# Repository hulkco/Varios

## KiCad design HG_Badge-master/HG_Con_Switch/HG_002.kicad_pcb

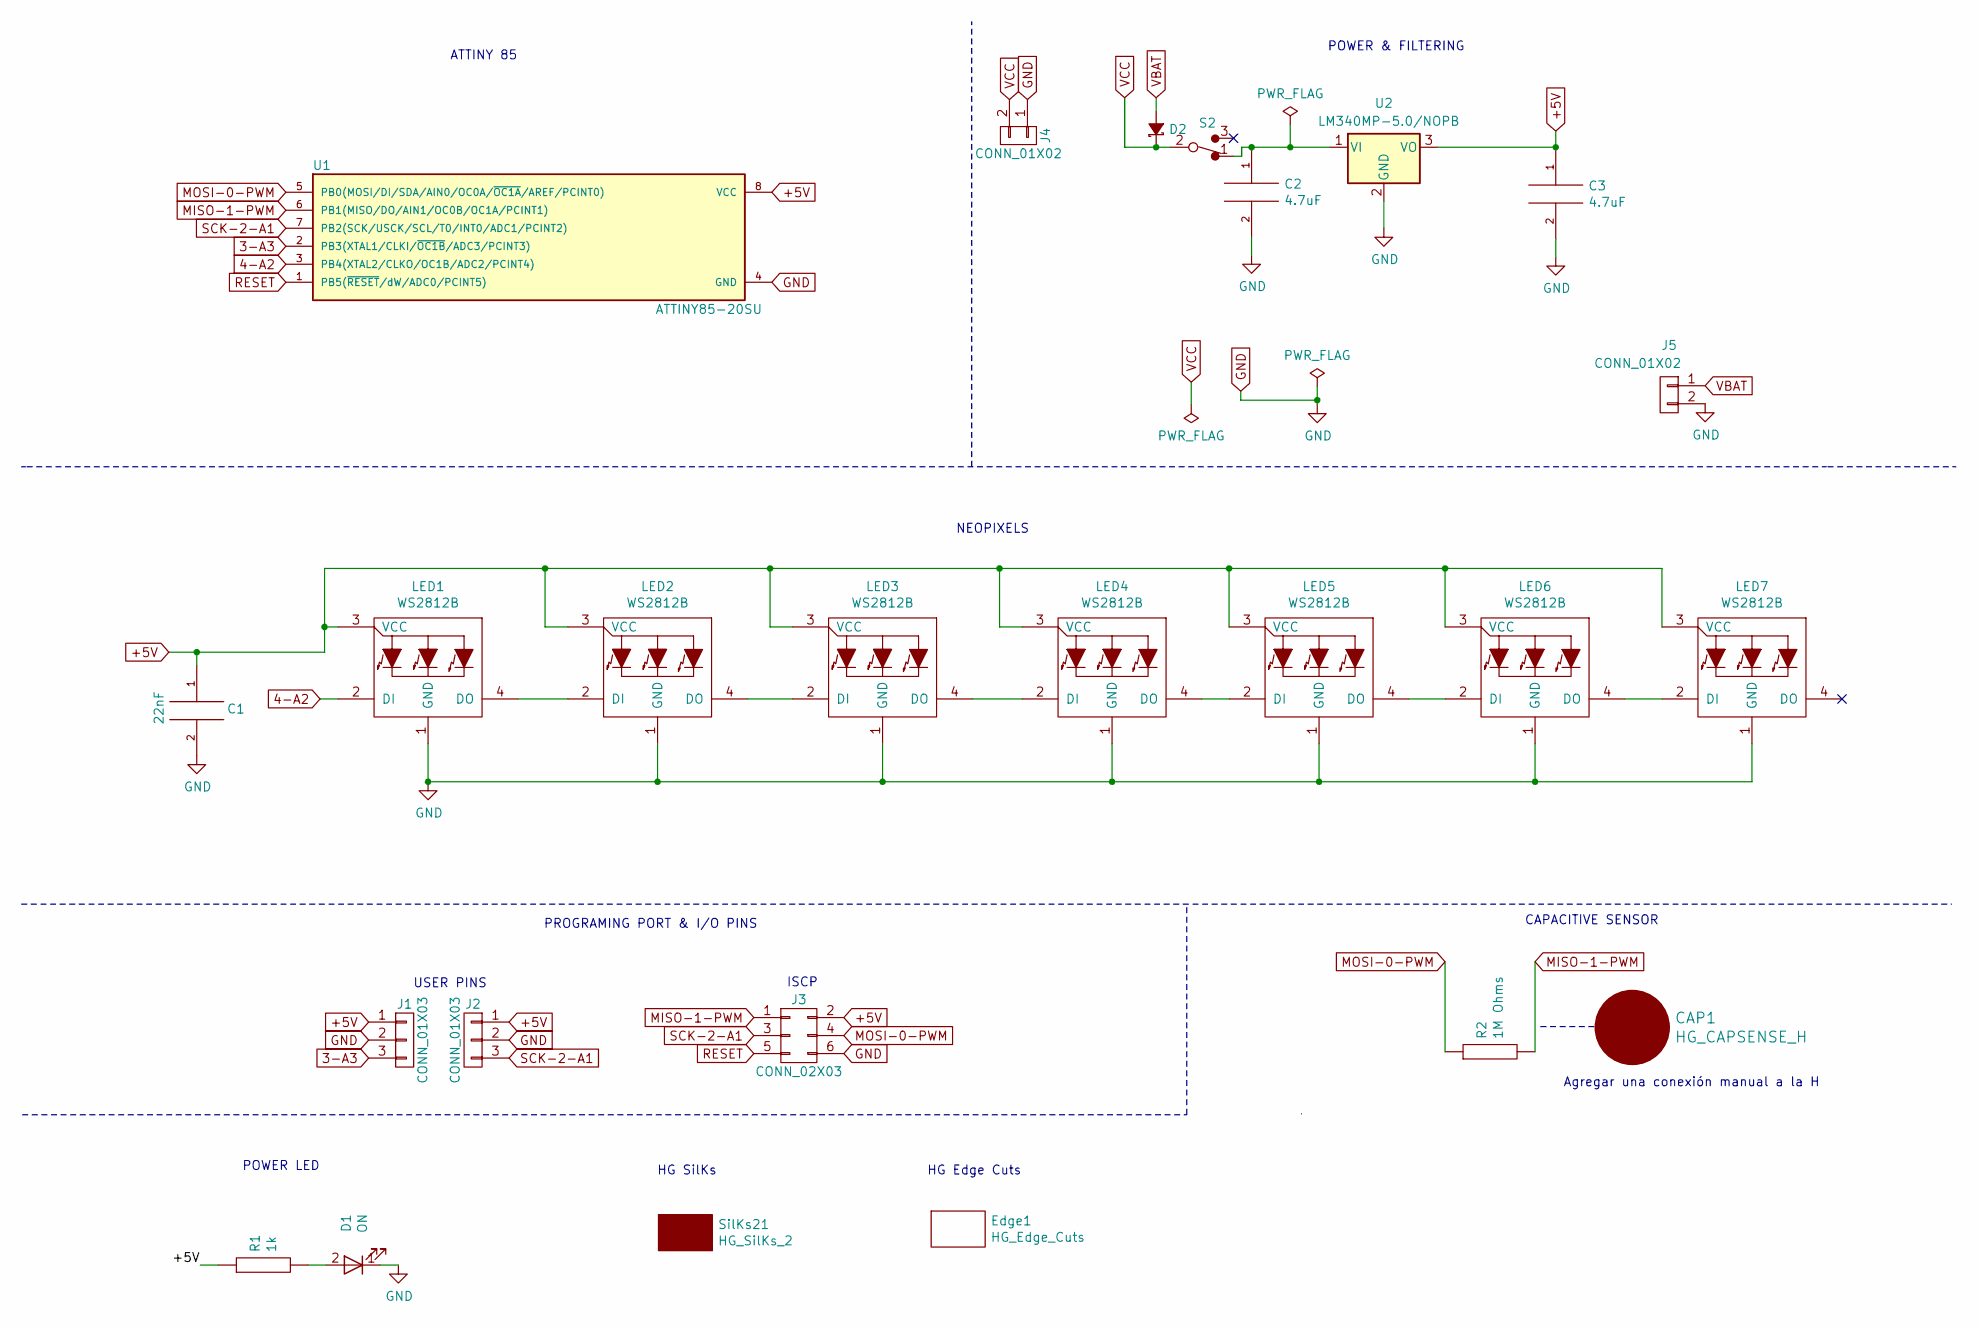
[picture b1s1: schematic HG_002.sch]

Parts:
C1: 22nF; C_1206_HandSoldering
C2, C3: 4.7uF; C_1206_HandSoldering
CAP1: HG_CAPSENSE_H; H_CapSense
D1: ON; LED_1206_HandSoldering
D2: MBRA140; DIODE-SMA
Edge1: HG_Edge_Cuts; HG_100_Edge_Cuts
J1: CONN_01X03; Pin_Header_Straight_1x03_Pitch2.54mm_SMD_Pin1Left
J2: CONN_01X03; Pin_Header_Straight_1x03_Pitch2.54mm_SMD_Pin1Right
J3: CONN_02X03; Pin_Header_Straight_2x03_Pitch2.54mm_SMD
J4: CONN_01X02; Pin_Header_Straight_1x02_Pitch2.54mm_SMD_Pin1Left
J5: CONN_01X02; Molex_PicoBlade_53261-0271_02x1.25mm_Angled
LED1, LED2, LED3, LED4, LED5, LED6, LED7: WS2812B
R1: 1k; R_1206_HandSoldering
R2: 1M Ohms; R_1206_HandSoldering
S2: MSK12C02_SWITCH-SLIDE-SPDT; MSK12C02
SilKs21: HG_SilKs_2; Corona_SilKs_3
U1: ATTINY85-20SU; SOIJ-8_5.3x5.3mm_Pitch1.27mm
U2: LM340MP-5.0/NOPB; SOT-223-3Lead_TabPin2

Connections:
3-A3: J1.3, U1.2 (PB3(XTAL1/CLKI/~OC1B~/ADC3/PCINT3))
4-A2: LED1.2 (DI), U1.3 (PB4(XTAL2/CLKO/OC1B/ADC2/PCINT4))
+5V: C1.1, C3.1, J1.1, J2.1, J3.2, LED1.3 (VCC), LED2.3 (VCC), LED3.3 (VCC), LED4.3 (VCC), LED5.3 (VCC), LED6.3 (VCC), LED7.3 (VCC), R1.1, U1.8 (VCC), U2.3 (VO)
GND: C1.2, C2.2, C3.2, D1.1 (K), J1.2, J2.2, J3.6, J4.1, J5.2, LED1.1 (GND), LED2.1 (GND), LED3.1 (GND), LED4.1 (GND), LED5.1 (GND), LED6.1 (GND), LED7.1 (GND), U1.4 (GND), U2.2 (GND)
MISO-1-PWM: J3.1, R2.2, U1.6 (PB1(MISO/DO/AIN1/OC0B/OC1A/PCINT1))
MOSI-0-PWM: J3.4, R2.1, U1.5 (PB0(MOSI/DI/SDA/AIN0/OC0A/~OC1A~/AREF/P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)
unnamed: C2.1, S2.1, U2.1 (VI)
unnamed: D1.2 (A), R1.2
unnamed: LED1.4 (DO), LED2.2 (DI)
unnamed: LED2.4 (DO), LED3.2 (DI)
unnamed: LED3.4 (DO), LED4.2 (DI)
unnamed: LED4.4 (DO), LED5.2 (DI)
unnamed: LED5.4 (DO), LED6.2 (DI)
unnamed: LED6.4 (DO), LED7.2 (DI)
RESET: J3.5, U1.1 (PB5(~RESET~/dW/ADC0/PCINT5))
SCK-2-A1: J2.3, J3.3, U1.7 (PB2(SCK/USCK/SCL/T0/INT0/ADC1/PCINT2))
VBAT: D2.2 (A), J5.1
VCC: D2.1 (K), J4.2, S2.2

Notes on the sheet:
POWER & FILTERING
ATTINY 85
NEOPIXELS
PROGRAMING PORT & I/O PINS
CAPACITIVE SENSOR
ISCP
USER PINS
POWER LED
HG Edge Cuts
HG SilKs
Agregar una conexión manual a la H

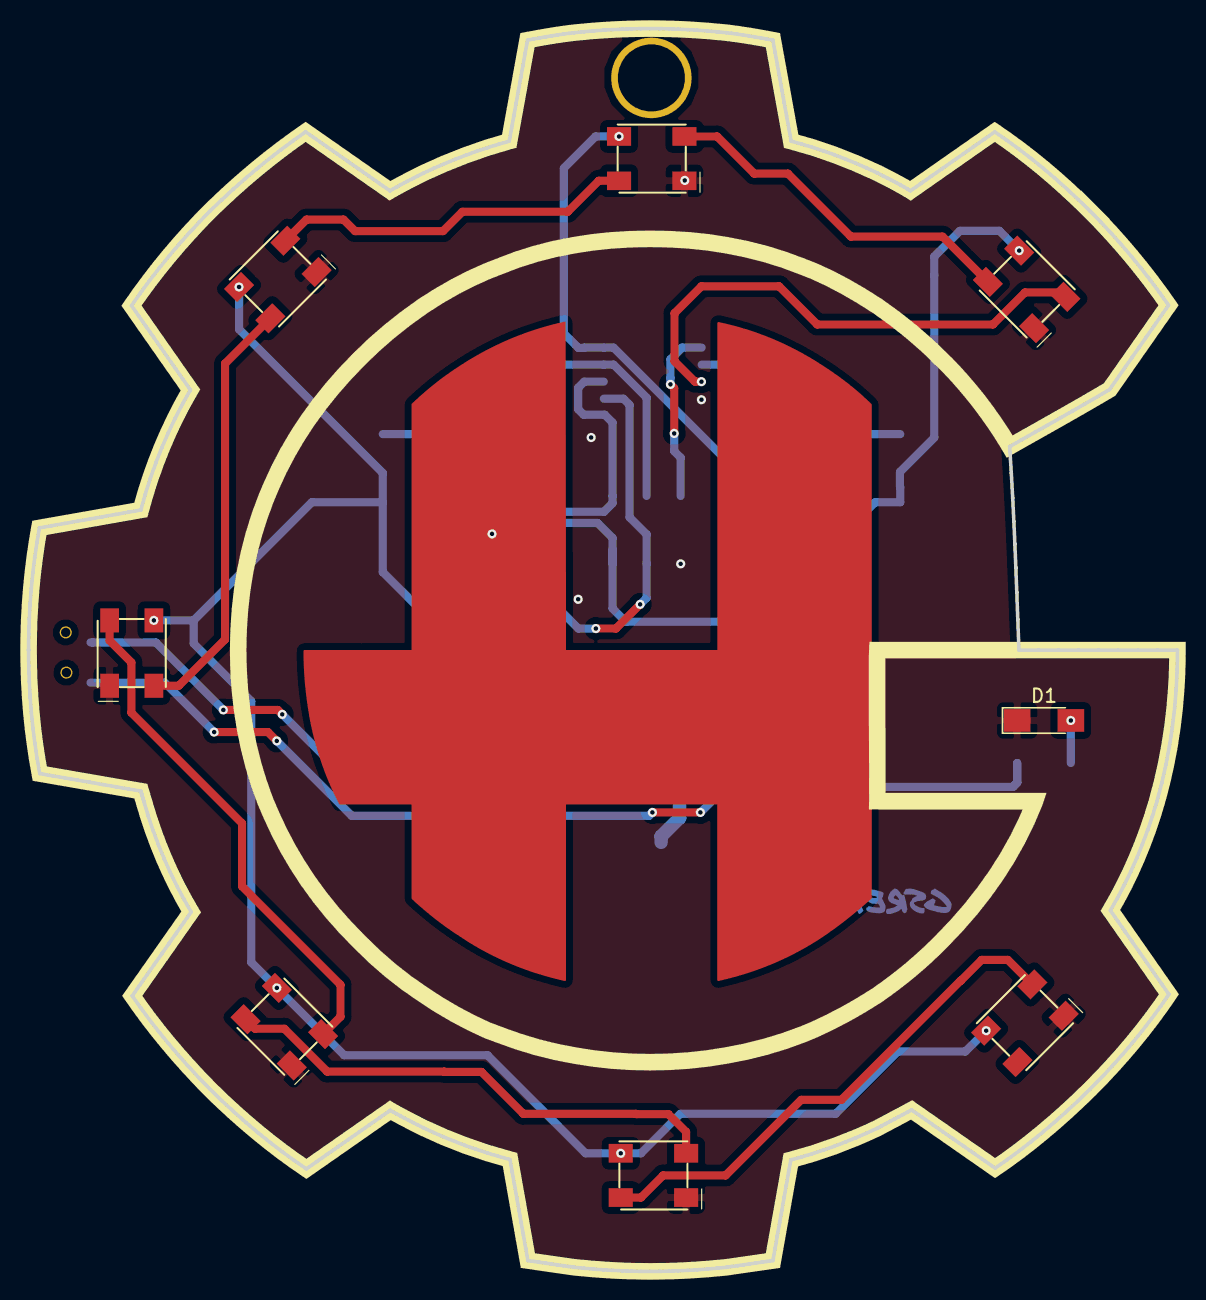
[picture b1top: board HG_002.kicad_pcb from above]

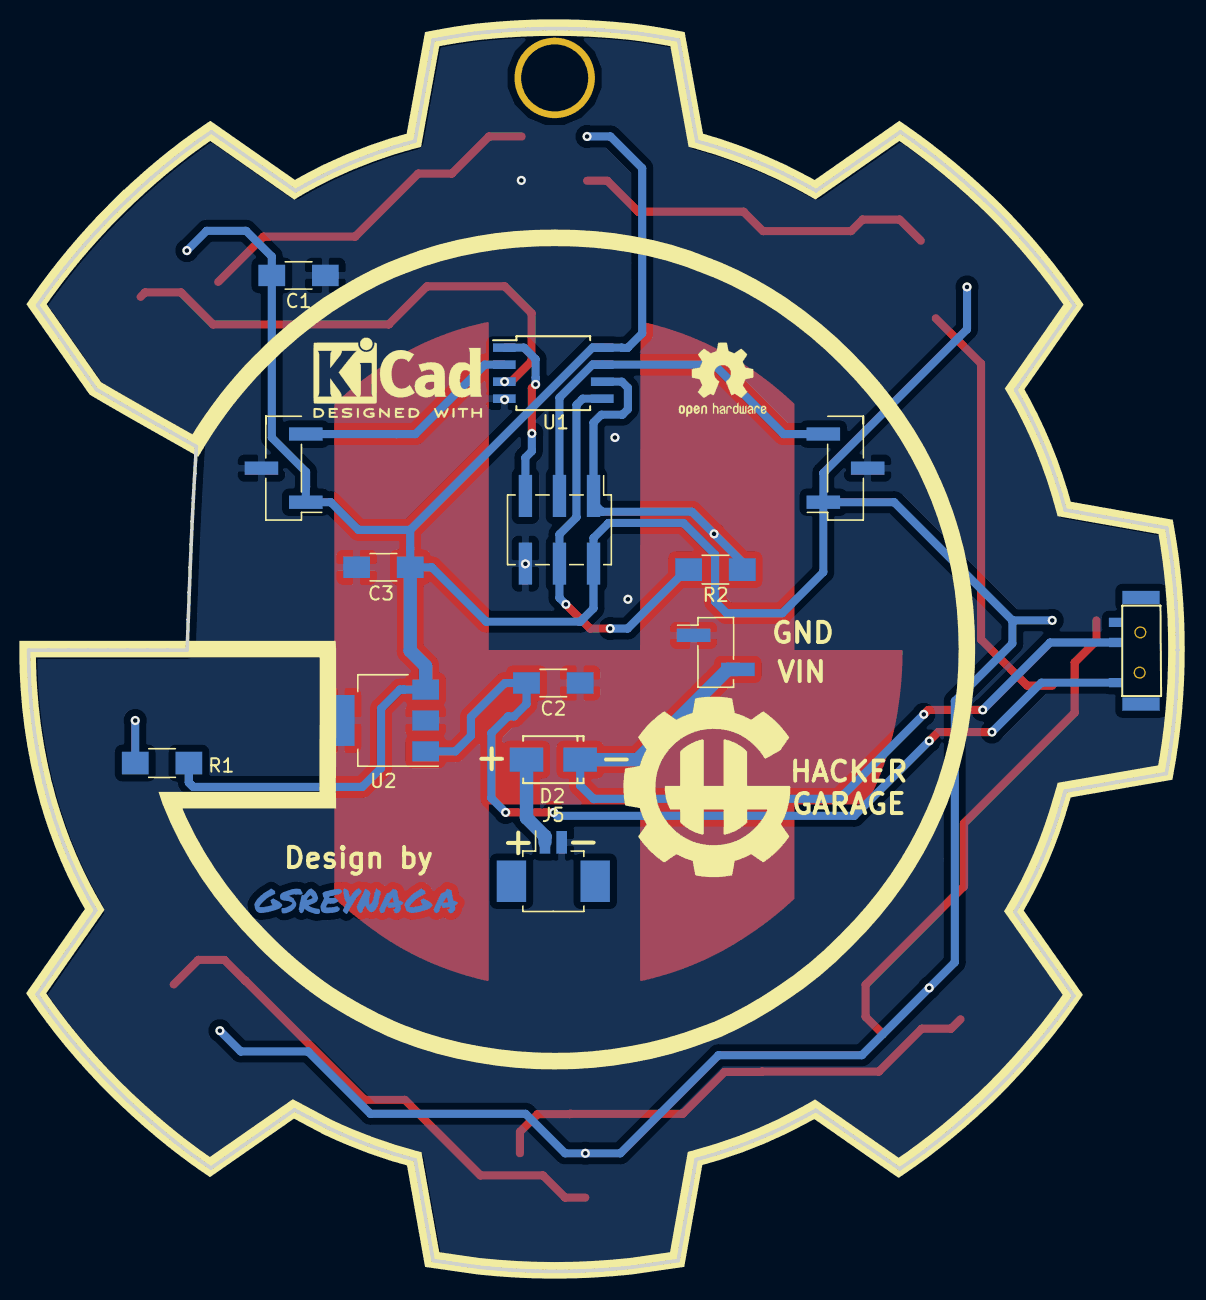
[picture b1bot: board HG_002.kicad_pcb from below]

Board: 2 copper layers, 85.7 x 92.7 mm, 28 parts (17 on the bottom side), 18 nets.

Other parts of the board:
MountinHoleBagde: MountingHole_5mm_Badge; MountingHole_3.5mm_Pad
svg2mod: G***; FirmaCuMask
svg2mod#2: G***; HG_SmallLogo
svg2mod#3: G***; HG_Edge.SilkS.2
svg2mod#4: G***; HG_SilkS.Back.2

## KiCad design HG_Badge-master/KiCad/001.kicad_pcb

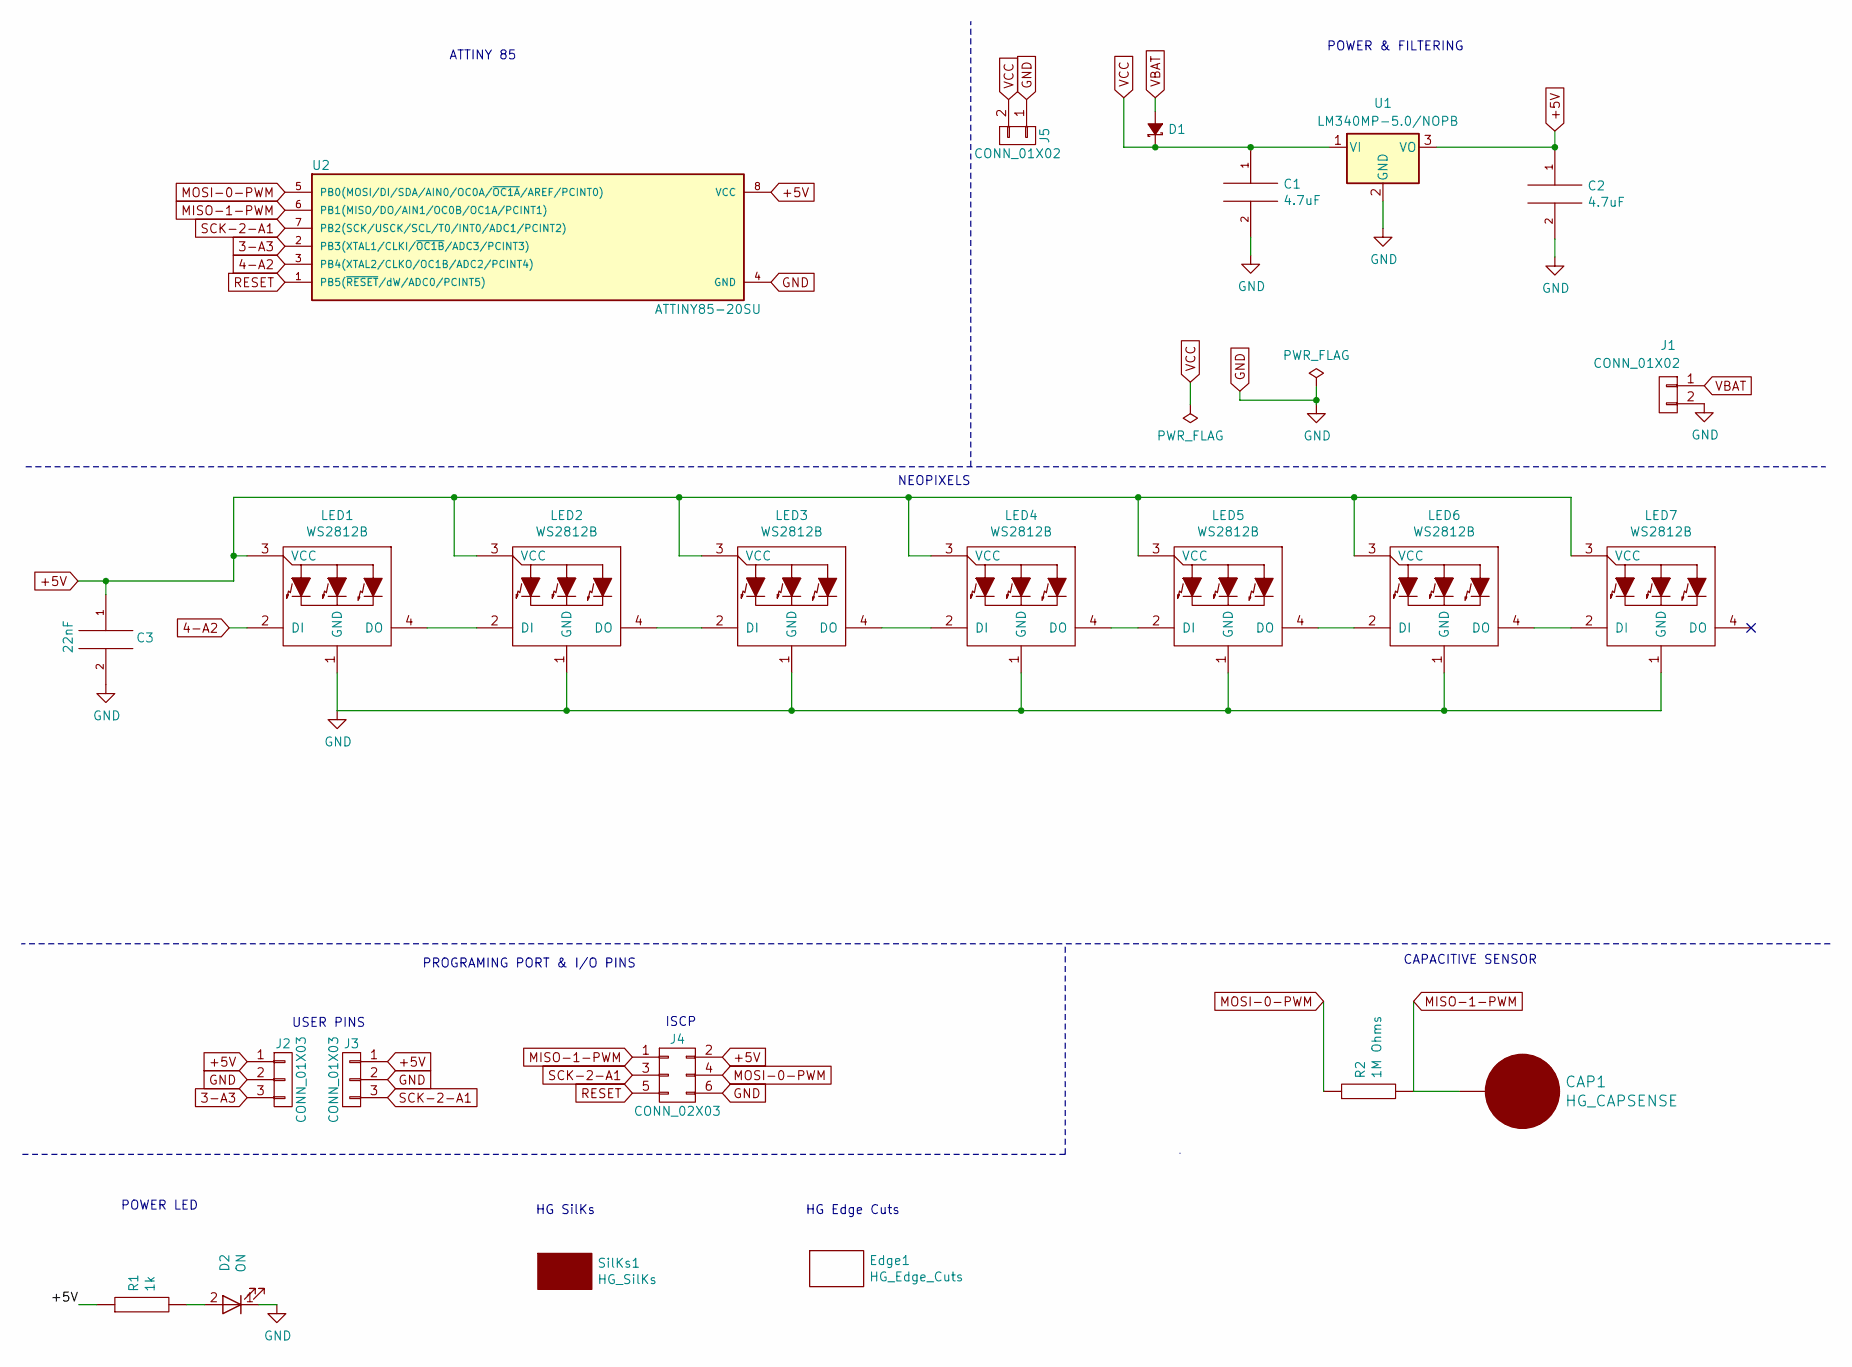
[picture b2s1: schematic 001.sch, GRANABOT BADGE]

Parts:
C1, C2: 4.7uF; C_1206_HandSoldering
C3: 22nF; C_1206_HandSoldering
CAP1: HG_CAPSENSE; H_CapSense
D1: MBRA140; DIODE-SMA
D2: ON; LED_1206_HandSoldering
Edge1: HG_Edge_Cuts; HG_100_Edge_Cuts
J1: CONN_01X02; Molex_PicoBlade_53261-0271_02x1.25mm_Angled
J2: CONN_01X03; Pin_Header_Straight_1x03_Pitch2.54mm_SMD_Pin1Left
J3: CONN_01X03; Pin_Header_Straight_1x03_Pitch2.54mm_SMD_Pin1Right
J4: CONN_02X03; Pin_Header_Straight_2x03_Pitch2.54mm_SMD
J5: CONN_01X02; Pin_Header_Straight_1x02_Pitch2.54mm_SMD_Pin1Left
LED1, LED2, LED3, LED4, LED5, LED6, LED7: WS2812B
R1: 1k; R_1206_HandSoldering
R2: 1M Ohms; R_1206_HandSoldering
SilKs1: HG_SilKs; Corona_SilKs
U1: LM340MP-5.0/NOPB; SOT-223-3Lead_TabPin2
U2: ATTINY85-20SU; SOIJ-8_5.3x5.3mm_Pitch1.27mm

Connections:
3-A3: J2.3, U2.2 (PB3(XTAL1/CLKI/~OC1B~/ADC3/PCINT3))
4-A2: LED1.2 (DI), U2.3 (PB4(XTAL2/CLKO/OC1B/ADC2/PCINT4))
+5V: C2.1, C3.1, J2.1, J3.1, J4.2, LED1.3 (VCC), LED2.3 (VCC), LED3.3 (VCC), LED4.3 (VCC), LED5.3 (VCC), LED6.3 (VCC), LED7.3 (VCC), R1.1, U1.3 (VO), U2.8 (VCC)
GND: C1.2, C2.2, C3.2, D2.1 (K), J1.2, J2.2, J3.2, J4.6, J5.1, LED1.1 (GND), LED2.1 (GND), LED3.1 (GND), LED4.1 (GND), LED5.1 (GND), LED6.1 (GND), LED7.1 (GND), U1.2 (GND), U2.4 (GND)
MISO-1-PWM: CAP1.1, J4.1, R2.2, U2.6 (PB1(MISO/DO/AIN1/OC0B/OC1A/PCINT1))
MOSI-0-PWM: J4.4, R2.1, U2.5 (PB0(MOSI/DI/SDA/AIN0/OC0A/~OC1A~/AREF/P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)
unnamed: D2.2 (A), R1.2
unnamed: LED1.4 (DO), LED2.2 (DI)
unnamed: LED2.4 (DO), LED3.2 (DI)
unnamed: LED3.4 (DO), LED4.2 (DI)
unnamed: LED4.4 (DO), LED5.2 (DI)
unnamed: LED5.4 (DO), LED6.2 (DI)
unnamed: LED6.4 (DO), LED7.2 (DI)
RESET: J4.5, U2.1 (PB5(~RESET~/dW/ADC0/PCINT5))
SCK-2-A1: J3.3, J4.3, U2.7 (PB2(SCK/USCK/SCL/T0/INT0/ADC1/PCINT2))
VBAT: D1.2 (A), J1.1
VCC: C1.1, D1.1 (K), J5.2, U1.1 (VI)

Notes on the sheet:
POWER & FILTERING
ATTINY 85
NEOPIXELS
PROGRAMING PORT & I/O PINS
CAPACITIVE SENSOR
ISCP
USER PINS
POWER LED
HG Edge Cuts
HG SilKs

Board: 2 copper layers, 24 parts (13 on the bottom side), 17 nets, no tracks yet.

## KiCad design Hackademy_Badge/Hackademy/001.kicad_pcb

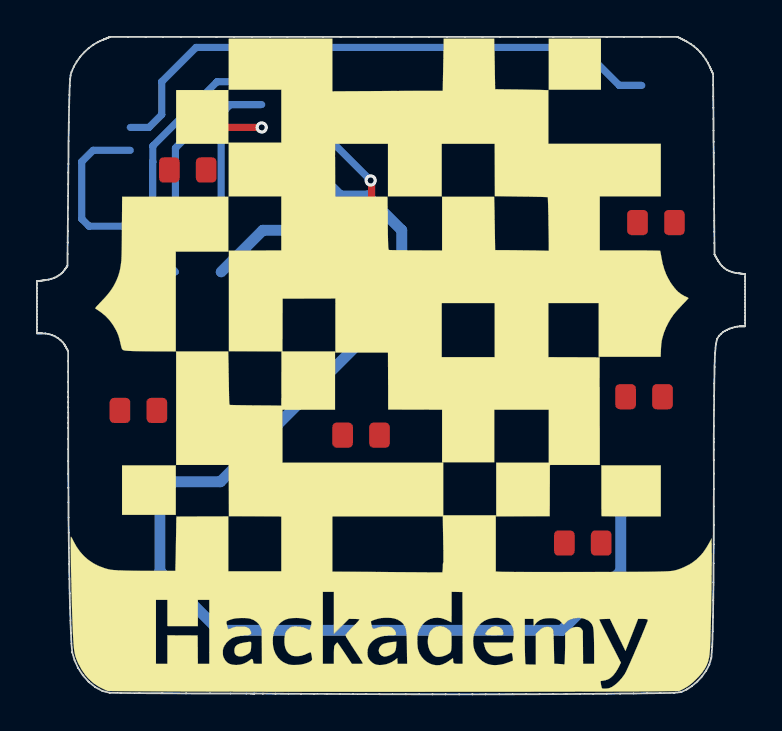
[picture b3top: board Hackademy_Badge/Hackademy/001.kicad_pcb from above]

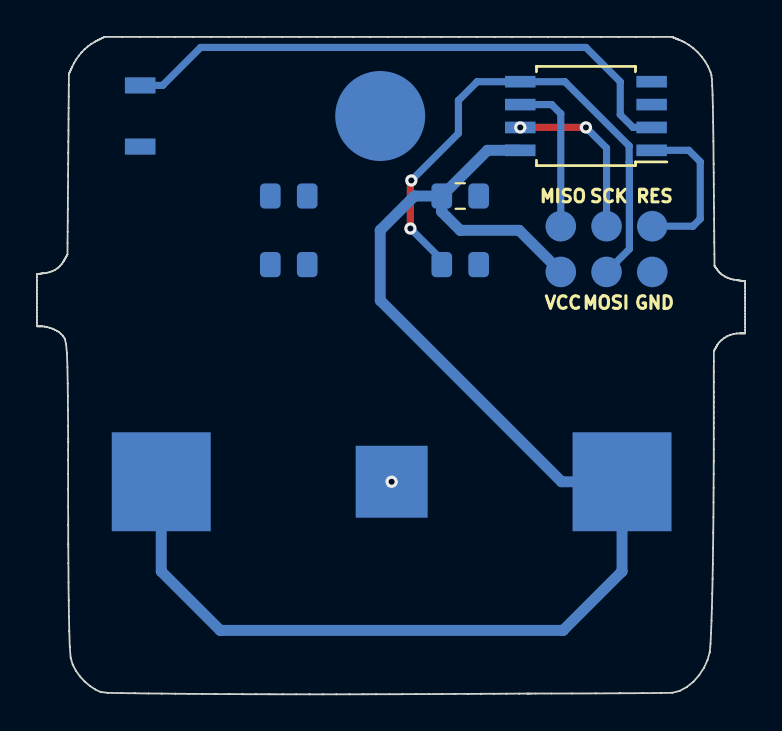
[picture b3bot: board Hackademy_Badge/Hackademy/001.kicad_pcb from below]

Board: 2 copper layers, 39.3 x 36.5 mm, 16 parts (9 on the bottom side), 10 nets.

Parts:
BT1: Battery; S8211R
C1: C_Small; C_0805
D1, D2, D3, D4, D5, D6: LED_Small_ALT; LED_0805
J1: Conn_02x03_Odd_Even; PogoPinSocket_2x03_P2.54mm
R1, R2, R3: 22 ohms; R_0805
Ref1: Edge.Cuts; Hackademy_01
Ref2: PinPad; Pin_Pad_D5.0mm
SW1: SW_Push; SW_SPST_B3U-1000P
U1: ATtiny85-20SU; SOIJ-8_5.3x5.3mm_P1.27mm

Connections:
+3V3: BT1.1, C1.2, J1.2, U1.8
GND: BT1.2, C1.1, J1.6, SW1.2, U1.4
unnamed: D1.1, D2.2, D3.2, D4.1, R2.1
unnamed: D1.2, D2.1, D5.2, D6.1, R1.1
unnamed: D3.1, D4.2, D5.1, D6.2, R3.1
PB0: J1.4, R1.2, U1.5
PB1: J1.1, R2.2, U1.6
PB2: J1.3, R3.2, U1.7
PB3: SW1.1, U1.2
PB5: J1.5, U1.1

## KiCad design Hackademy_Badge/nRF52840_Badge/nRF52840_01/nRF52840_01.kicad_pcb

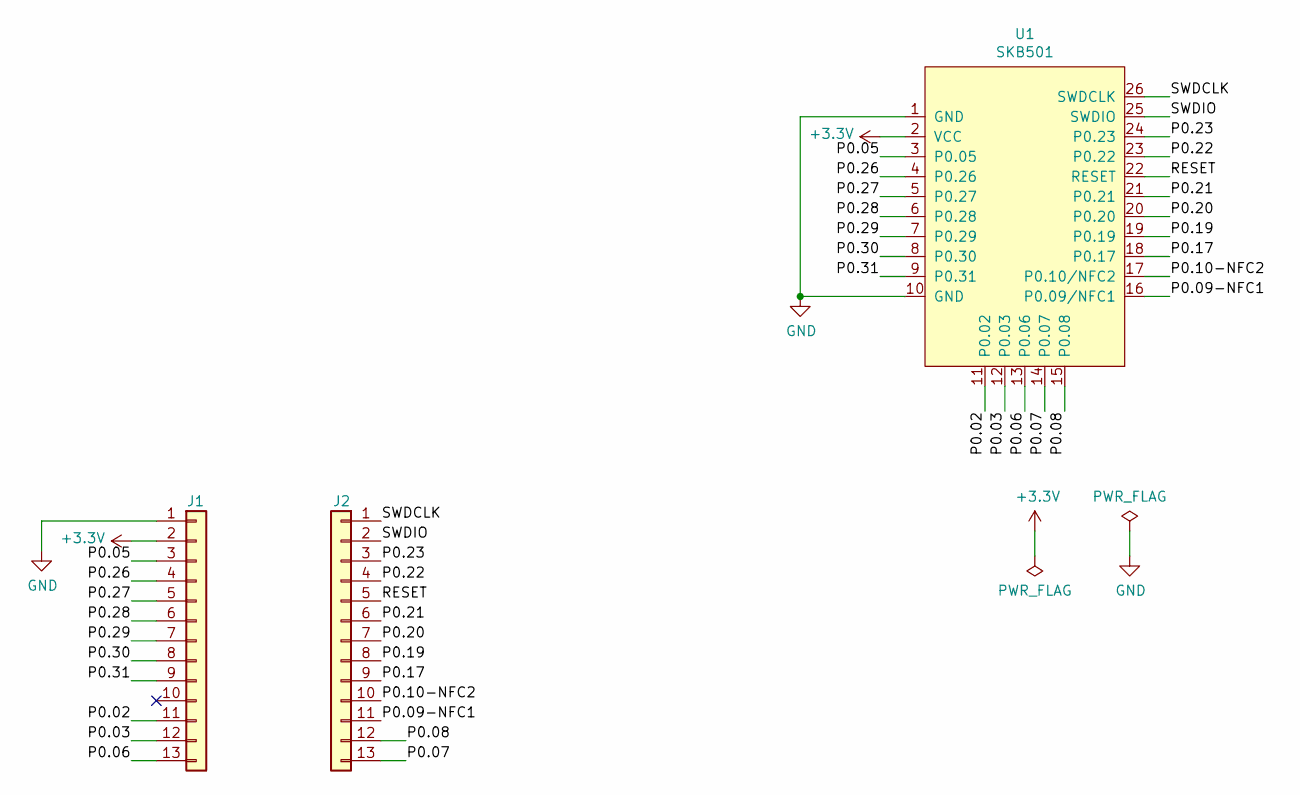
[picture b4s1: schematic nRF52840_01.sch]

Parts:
J1, J2: Conn_01x13; PinSocket_1x13
U1: SKB501; SKB501_Footprint

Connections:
+3V3: J1.2, U1.2 (VCC)
/P0.02: J1.11, U1.11 (P0.02)
/P0.03: J1.12, U1.12 (P0.03)
/P0.05: J1.3, U1.3 (P0.05)
/P0.06: J1.13, U1.13 (P0.06)
/P0.07: J2.13, U1.14 (P0.07)
/P0.08: J2.12, U1.15 (P0.08)
/P0.09-NFC1: J2.11, U1.16 (P0.09/NFC1)
/P0.10-NFC2: J2.10, U1.17 (P0.10/NFC2)
/P0.17: J2.9, U1.18 (P0.17)
/P0.19: J2.8, U1.19 (P0.19)
/P0.20: J2.7, U1.20 (P0.20)
/P0.21: J2.6, U1.21 (P0.21)
/P0.22: J2.4, U1.23 (P0.22)
/P0.23: J2.3, U1.24 (P0.23)
/P0.26: J1.4, U1.4 (P0.26)
/P0.27: J1.5, U1.5 (P0.27)
/P0.28: J1.6, U1.6 (P0.28)
/P0.29: J1.7, U1.7 (P0.29)
/P0.30: J1.8, U1.8 (P0.30)
/P0.31: J1.9, U1.9 (P0.31)
/RESET: J2.5, U1.22 (RESET)
/SWDCLK: J2.1, U1.26 (SWDCLK)
/SWDIO: J2.2, U1.25 (SWDIO)
GND: J1.1, U1.1 (GND), U1.10 (GND)

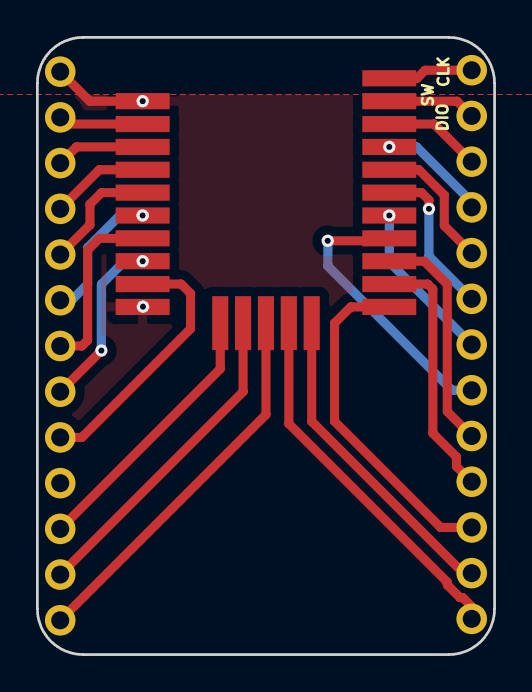
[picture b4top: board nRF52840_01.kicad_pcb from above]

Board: 2 copper layers, 25.4 x 34.3 mm, 3 parts (0 on the bottom side), 25 nets.

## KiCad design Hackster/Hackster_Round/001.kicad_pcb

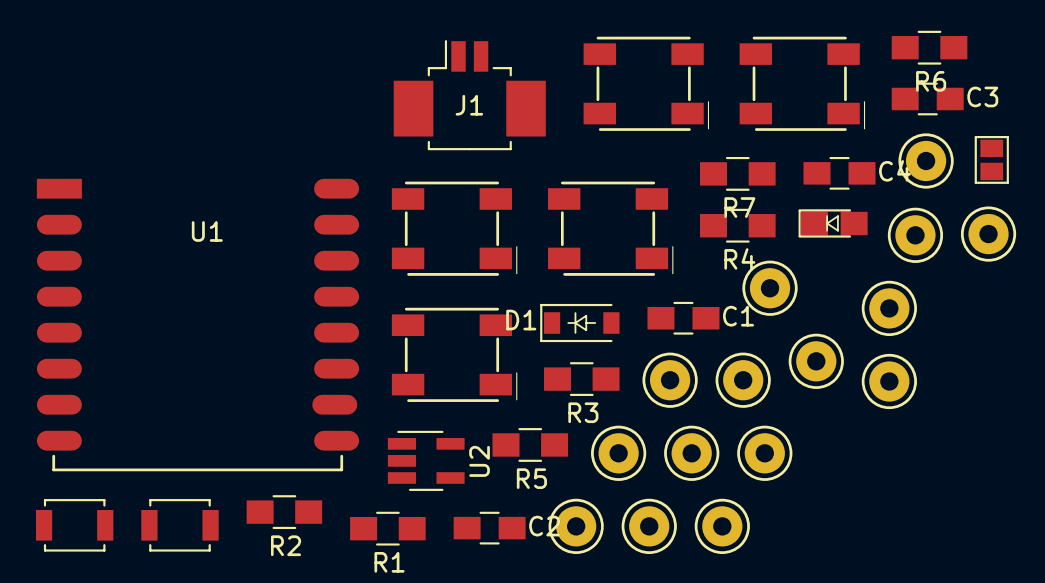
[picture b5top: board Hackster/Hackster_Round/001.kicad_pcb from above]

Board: 2 copper layers, 39 parts (0 on the bottom side), 24 nets, no tracks yet.

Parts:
C1, C2: 10uF; C_0805_HandSoldering
C3: 22nF; C_0805_HandSoldering
C4: 1uF; C_0805_HandSoldering
D1: MBRA140; D_SOD-123
D2: ON; LED_0805
J1: CONN_01X02; Molex_PicoBlade_53261-0271_02x1.25mm_Angled
J2, J3, J4, J5, J6, J7, J8, J9, J10, J11, J12, J13, J14, J15, J16: TEST_1P; CONN-HEADER-STRAIGHT-P2.54MM-1x01
J17: GS2
LED1, LED2, LED3, LED4, LED5: WS2812B
R1, R3, R4, R5, R6, R7: 10k; R_0805_HandSoldering
R2: 1k; R_0805_HandSoldering
SW1: USER/PROG; SW_SPST_B3U-1000P
SW2: RESET; SW_SPST_B3U-1000P
U1: ESP-12; ESP-12S_SMD
U2: SPX3819M5-L-3-3/TR; SOT-23-5_HandSoldering

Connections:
+3.3V: C2.1, C3.1, C4.1, LED1.3, LED2.3, LED3.3, LED4.3, LED5.3, R1.1, R2.1, R3.1, R4.1, R7.1, U1.8, U2.5
ADC: J4.1, U1.2
CH_PD: J6.1, R4.2, U1.3
GND: C1.2, C2.2, C3.2, C4.2, D2.1, J1.2, J16.1, LED1.1, LED2.1, LED3.1, LED4.1, LED5.1, R6.1, SW1.1, SW2.1, U1.9, U2.2
GPIO0: J11.1, R3.2, SW1.2, U1.12
GPIO2: LED1.2, R7.2, U1.11
GPIO4: J9.1, U1.13
GPIO5: J7.1, U1.14
GPIO12: J10.1, U1.6
GPIO13: J12.1, U1.7
GPIO14: J8.1, U1.5
GPIO15: J13.1, R6.2, U1.10
GPIO16: J14.1, J17.2, U1.4
unnamed: D2.2, R2.2
unnamed: LED1.4, LED2.2
unnamed: LED2.4, LED3.2
unnamed: LED3.4, LED4.2
unnamed: LED4.4, LED5.2
unnamed: R5.2, U2.3
REST: J2.1, J17.1, R1.2, SW2.2, U1.1
RXD: J5.1, U1.15
TXD: J3.1, U1.16
VBAT: D1.2, J1.1
VCC: C1.1, D1.1, J15.1, R5.1, U2.1

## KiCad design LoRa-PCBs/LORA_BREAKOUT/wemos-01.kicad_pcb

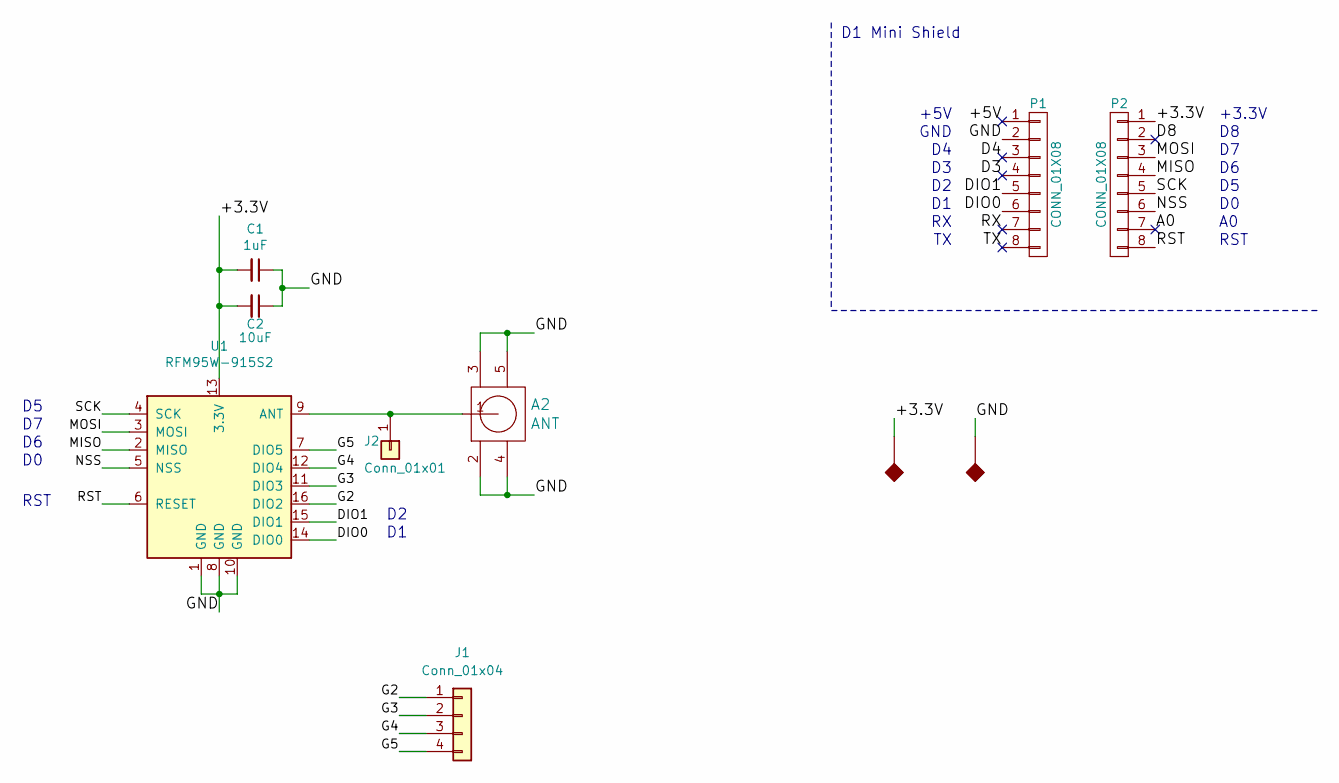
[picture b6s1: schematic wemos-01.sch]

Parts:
A2: ANT; SMA_EDGELAUNCH_UFL_WeMos_Lora
C1: 1uF; C_0805_2012Metric_Pad1.29x1.40mm_HandSolder
C2: 10uF; C_0805_2012Metric_Pad1.29x1.40mm_HandSolder
J1: Conn_01x04; PinSocket_1x04_P2.54mm_WeMos
J2: Conn_01x01; PinSocket_1x01_P2.54mm_WeMos
P1, P2: CONN_01X08; D1_mini_Pin_Header
U1: RFM95W-915S2; HOPERF_RFM9XW_SMD_WeMos

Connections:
/+3.3V: C1.2, C2.2, P2.1, U1.13 (3.3V)
/+5V: P1.1
/A0: P2.7
/D3: P1.4
/D4: P1.3
/D8: P2.2
/DIO0: P1.6, U1.14 (DIO0)
/DIO1: P1.5, U1.15 (DIO1)
/G2: J1.1, U1.16 (DIO2)
/G3: J1.2, U1.11 (DIO3)
/G4: J1.3, U1.12 (DIO4)
/G5: J1.4, U1.7 (DIO5)
/GND: A2.2, A2.3, A2.4, A2.5, C1.1, C2.1, P1.2, U1.1 (GND), U1.8 (GND), U1.10 (GND)
/MISO: P2.4, U1.2 (MISO)
/MOSI: P2.3, U1.3 (MOSI)
/NSS: P2.6, U1.5 (NSS)
/RST: P2.8, U1.6 (RESET)
/RX: P1.7
/SCK: P2.5, U1.4 (SCK)
/TX: P1.8
unnamed: A2.1, J2.1, U1.9 (ANT)

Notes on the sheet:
D1 Mini Shield
+3.3V
+5V
GND
RST

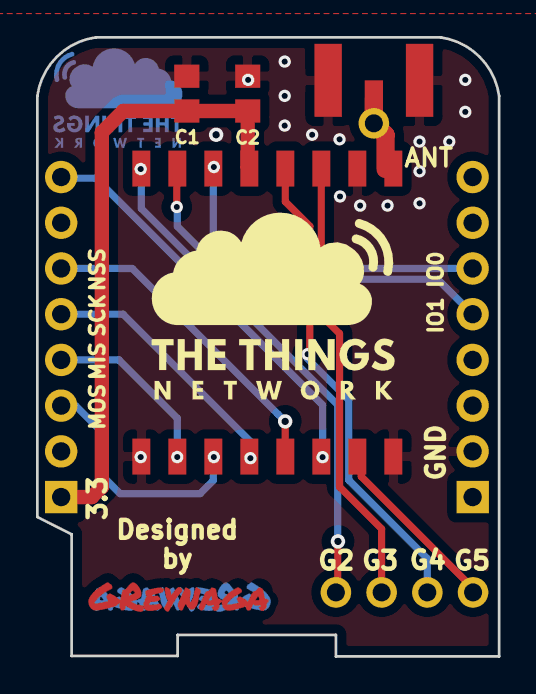
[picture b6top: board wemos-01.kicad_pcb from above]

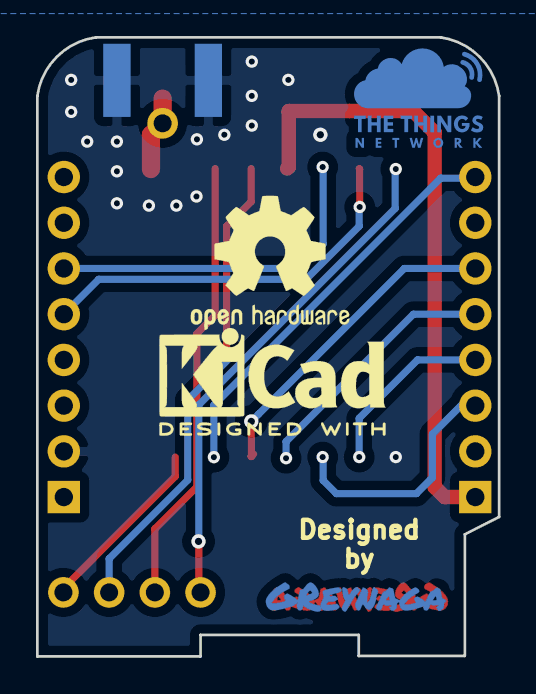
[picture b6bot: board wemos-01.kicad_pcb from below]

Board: 2 copper layers, 25.7 x 34.4 mm, 12 parts (4 on the bottom side), 14 nets.

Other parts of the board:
Ref**: Val**; Feather_CU
Ref**#2: Val**; Feather_CU
svg2mod: G***; ttn_logoCu1
svg2mod#2: G***; ttn_logo3
